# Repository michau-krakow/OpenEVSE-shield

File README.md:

OpenEVSE shield for Adruino Mega2560

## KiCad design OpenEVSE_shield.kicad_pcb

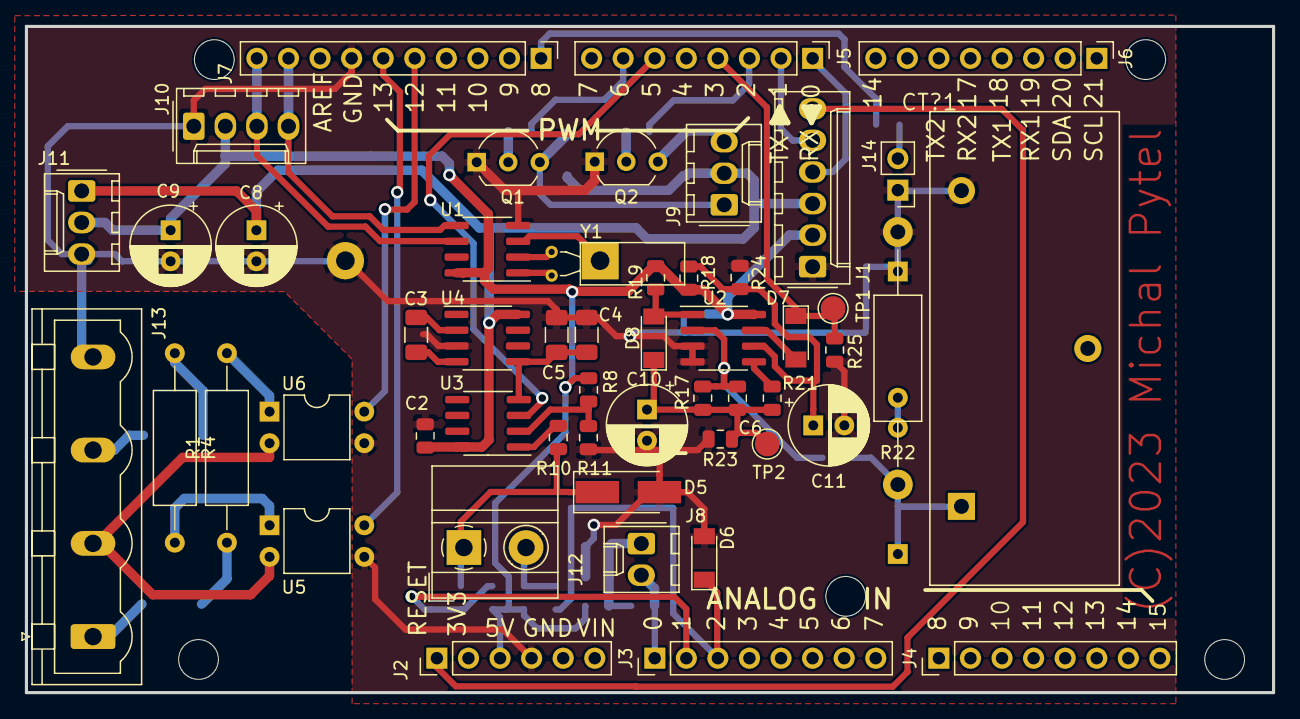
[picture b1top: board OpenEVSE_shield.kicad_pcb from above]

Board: 2 copper layers, 100.3 x 53.6 mm, 78 parts (0 on the bottom side), 49 nets.

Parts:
@HOLE0, @HOLE1, @HOLE2, @HOLE3, @HOLE5: (no value)
BT1: Battery_Cell; BatteryHolder_Keystone_103_1x20mm
C1, C2, C7: 0.1u; C_0805_2012Metric
C3, C4, C5: 10u; C_1206_3216Metric
C6: 100n; C_0805_2012Metric
C8, C9, C10, C11: 10u; CP_Radial_D6.3mm_P2.50mm
CT?1: AC1050
D1, D4: SM4007; D_MELF
D2, D3, D6, D7, D8: LL4148; D_MiniMELF
D5: P6SMB16CA; D_SMA_Handsoldering
D9, D10: BZX55-4V7; D_DO-35_SOD27_P10.16mm_Horizontal
J1: COMMS; Molex_KK-254_AE-6410-06A_1x06_P2.54mm_Vertical
J2: Conn_01x06; PinHeader_1x06_P2.54mm_Vertical
J3, J4, J5, J6: Conn_01x08; PinHeader_1x08_P2.54mm_Vertical
J7: Conn_01x10; PinHeader_1x10_P2.54mm_Vertical
J8: AMP; Molex_KK-254_AE-6410-02A_1x02_P2.54mm_Vertical
J9: DC_RELAY; Molex_KK-254_AE-6410-03A_1x03_P2.54mm_Vertical
J10: LCD; Molex_KK-254_AE-6410-04A_1x04_P2.54mm_Vertical
J11: PSU; Molex_KK-254_AE-6410-03A_1x03_P2.54mm_Vertical
J12: PILOT; TerminalBlock_MetzConnect_Type011_RT05502HBWC_1x02_P5.00mm_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
J13: MAINS; PhoenixContact_GMSTBVA_2,5_4-G_1x04_P7.50mm_Vertical
J14: GFCI_TEST; PinHeader_1x02_P2.54mm_Vertical
Q1, Q2: PN2222A; TO-92_Inline_Wide
R1, R4: 330k; R_Axial_DIN0309_L9.0mm_D3.2mm_P15.24mm_Horizontal
R2: 33; R_0805_2012Metric
R3, R5, R8, R11, R15: 100k; R_0805_2012Metric
R6, R7: 330; R_0805_2012Metric
R9, R20: 1k; R_0805_2012Metric
R10: 620; R_0805_2012Metric
R12: 200k; R_0805_2012Metric
R13, R18, R25: 10k; R_0805_2012Metric
R14: 56k; R_0805_2012Metric
R16: 470; R_0805_2012Metric
R17: 470k; R_0805_2012Metric
R19: 22k; R_0805_2012Metric
R21: 100; R_0805_2012Metric
R22: 500; R_Axial_DIN0411_L9.9mm_D3.6mm_P20.32mm_Horizontal
R23: NOT FITTED; R_0805_2012Metric
R24: 8k2; R_0805_2012Metric
TP1, TP2: TestPoint_Alt; TestPoint_Pad_D2.0mm
U1: DS1307Z+; SOIC-8_3.9x4.9mm_P1.27mm
U2: LM358; SOIC-8_3.9x4.9mm_P1.27mm
U3: TL072; SOIC-8_3.9x4.9mm_P1.27mm
U4: ICL7660; SOIC-8_3.9x4.9mm_P1.27mm
U5, U6: LTV-814; DIP-4_W7.62mm
Y1: 32,768kHz; Crystal_C38-LF_D3.0mm_L8.0mm_Horizontal

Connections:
+5V: C7.1, C9.1, J1.2, J2.3, J10.2, J11.2, R3.1, R8.1, R9.1, R14.1, R18.1, R19.1, U1.8, U2.8
+12V: C2.2, C8.1, D2.1, D3.1, J1.3, J9.2, J11.1, U3.8, U4.8
-12V: C4.1, C5.1, U3.4, U4.5
/AC_TEST_L1: J7.5, U6.4
/AC_TEST_L2: J7.6, U5.4
/AMP_READ: J3.1, J8.2, R2.1
/CP: D5.1, J12.1, R10.1, R12.1
/DC_RELAY_1: J5.7, R6.2
/DC_RELAY_2: J5.3, R7.2
/GFCI_INT: D7.1, J5.4, R25.1, TP1.1
/GFCI_TEST: J7.1, R16.1
/L1_TEST: D1.2, J13.1
/L2_TEST: D4.2, J13.3
/N: J13.2, U5.2, U6.2
/PILOTREAD: J3.2, R12.2, R14.2, R15.1
/PP: J12.2, R9.2, R13.1
/PP_READ: D6.1, J3.3, R13.2
/PWM: J5.6, U3.3
/RST: J1.6, J2.1
/RX-I: J1.4, J5.1
/SCL: J7.10, J10.3, U1.6
/SDA: J7.9, J10.4, U1.5
/TX: J1.5, J5.2
GND: BT1.2, C1.2, C2.1, C4.2, C5.2, C7.2, C8.2, C9.2, C10.2, C11.2, CT?1.P$2, D5.2, D6.2, D10.1, J1.1, J2.4, J7.7, J10.1, J11.3, J13.4, J14.1, Q1.1, Q2.1, R5.2, R11.2, R15.2, R22.2, R23.2, R24.2, R25.2, U1.4, U2.3, U2.4, U4.3, U5.3, U6.3
unnamed: BT1.1, U1.3
unnamed: C1.1, J8.1, R2.2, R3.2, R5.1
unnamed: C3.1, U4.2
unnamed: C3.2, U4.4
unnamed: C6.1, R17.2, R20.1, U2.2
unnamed: C6.2, C10.1, D8.1, R17.1, R21.2, R23.1, TP2.1
unnamed: C11.1, R18.2, R24.1, U2.6
unnamed: CT?1.P$1, D9.1, R20.2, R22.1
unnamed: D1.1, R1.1
unnamed: D2.2, J9.1, Q1.3
unnamed: D3.2, J9.3, Q2.3
unnamed: D4.1, R4.1
unnamed: D7.2, U2.7
unnamed: D8.2, R19.2, U2.1
unnamed: D9.2, D10.2
unnamed: J14.2, R16.2
unnamed: Q1.2, R6.1
unnamed: Q2.2, R7.1
unnamed: R1.2, U6.1
unnamed: R4.2, U5.1
unnamed: R10.2, U3.1
unnamed: R8.2, R11.1, U3.2
unnamed: R21.1, U2.5
unnamed: U1.1, Y1.1
unnamed: U1.2, Y1.2

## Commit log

2023-02-01 Version 1 of KiCad project sent to production
2023-02-02 Gerber files for first production order
2023-02-19 Rename project files
2023-02-19 Add 3D model for Talema AC1050 current transformer
2023-02-19 fix: Add missing optocouplers connections on PCB
2023-02-19 fix: missing GND connection at ICL7660
2023-02-19 fix DRC errors, align overlay colliding with soldering pads
2023-02-19 Tweak values during assembly and testing

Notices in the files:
OpenEVSE_shield.kicad_pcb:
(C)2023 Michal Pytel
